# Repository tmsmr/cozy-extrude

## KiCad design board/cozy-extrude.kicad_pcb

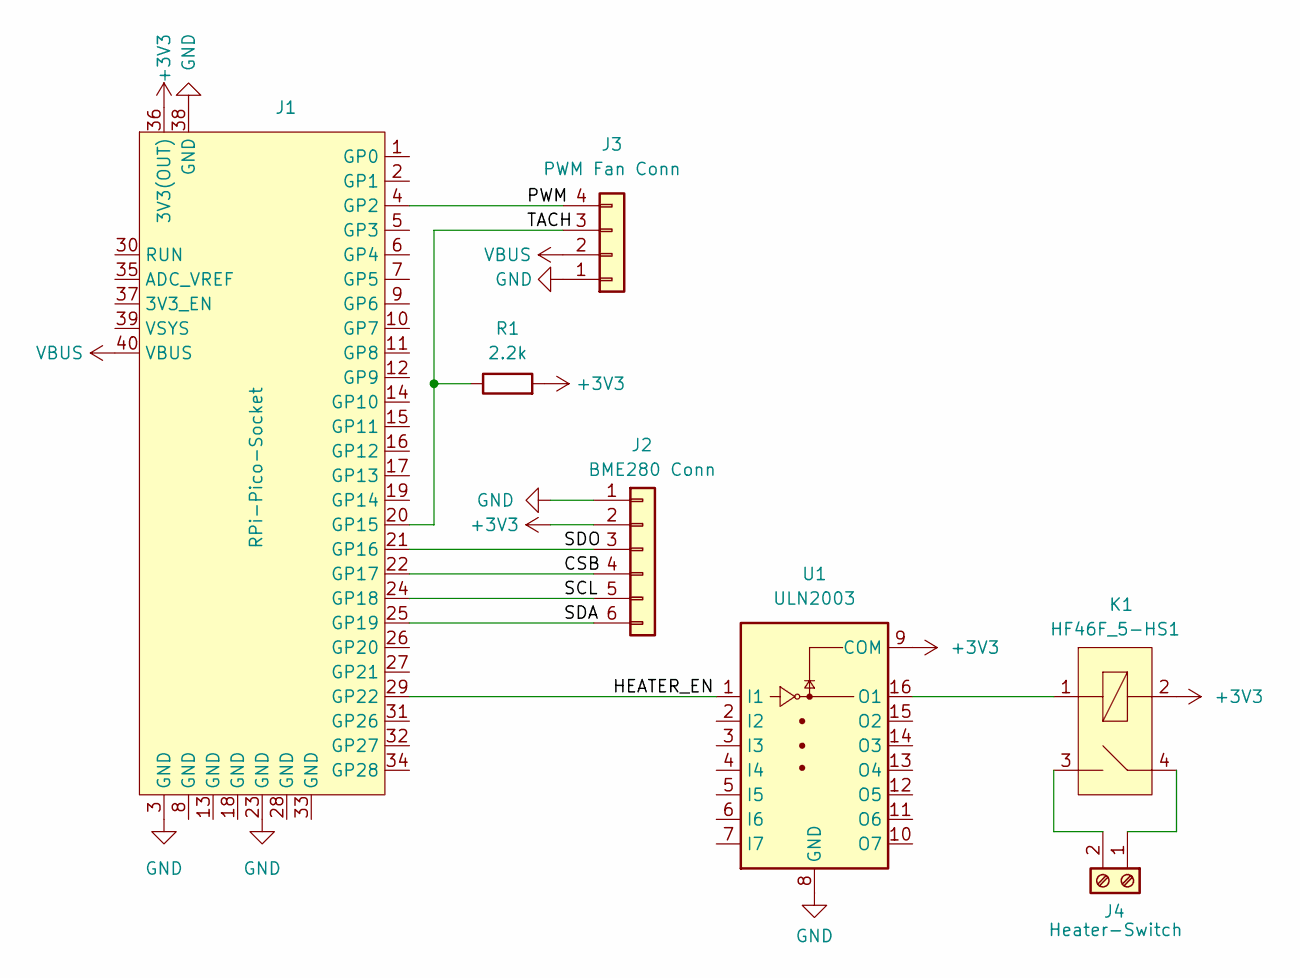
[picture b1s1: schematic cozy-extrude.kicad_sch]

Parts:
J1: RPi-Pico-Socket
J2: BME280 Conn; PinHeader_1x06_P2.54mm_Vertical
J3: PWM Fan Conn; Molex_KK-254_AE-6410-04A_1x04_P2.54mm_Vertical
J4: Heater-Switch; TerminalBlock_Phoenix_MKDS-1,5-2-5.08_1x02_P5.08mm_Horizont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
K1: HF46F_5-HS1; HF46F
R1: 2.2k; R_Axial_DIN0309_L9.0mm_D3.2mm_P15.24mm_Horizontal
U1: ULN2003; DIP-16_W7.62mm

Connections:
+3V3: J1.36 (3V3(OUT)), J2.2, K1.2, R1.2, U1.9 (COM)
/CSB: J1.22 (GP17), J2.4
/HEATER_EN: J1.29 (GP22), U1.1 (I1)
/PWM: J1.4 (GP2), J3.4
/SCL: J1.24 (GP18), J2.5
/SDA: J1.25 (GP19), J2.6
/SDO: J1.21 (GP16), J2.3
/TACH: J1.20 (GP15), J3.3, R1.1
GND: J1.3 (GND), J1.23 (GND), J1.38 (GND), J2.1, J3.1, U1.8 (GND)
unnamed: K1.1, U1.16 (O1)
unnamed: J4.2, K1.3
unnamed: J4.1, K1.4
VBUS: J1.40 (VBUS), J3.2

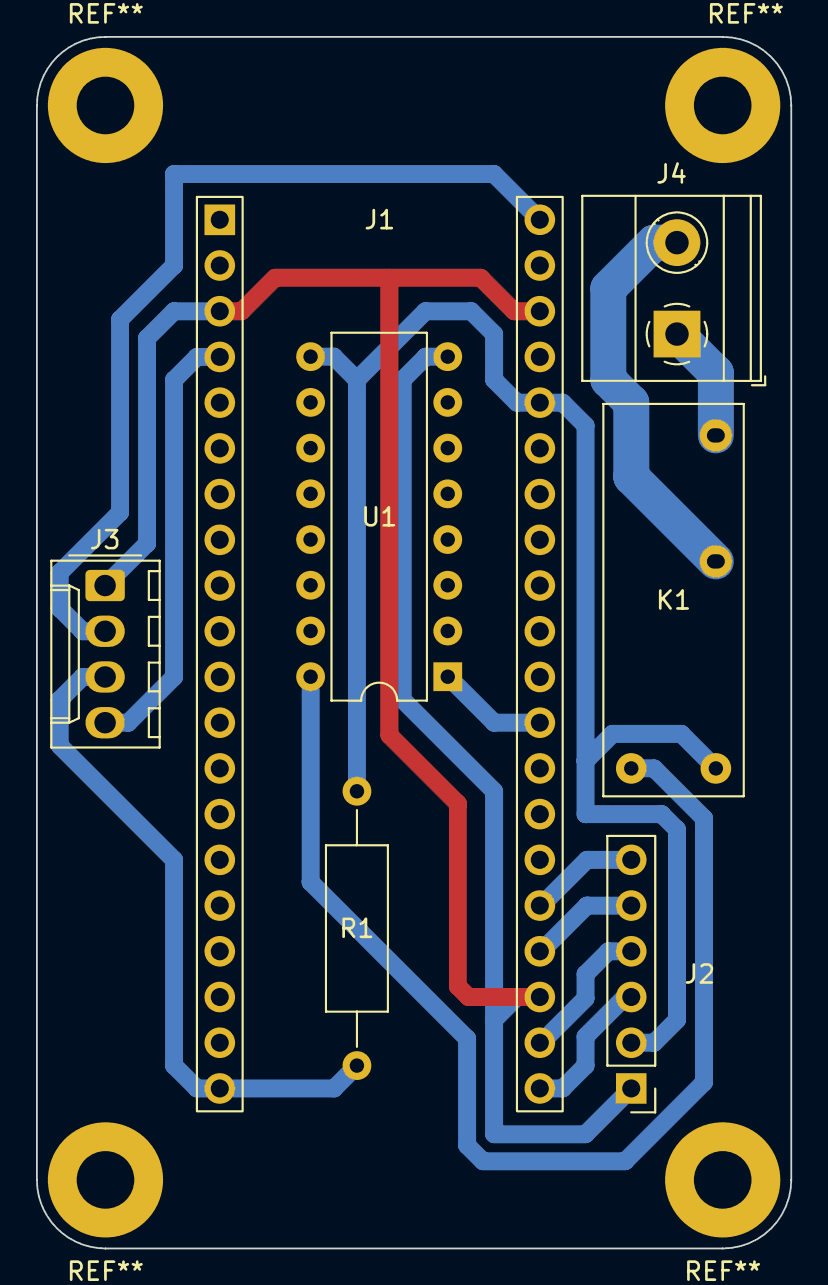
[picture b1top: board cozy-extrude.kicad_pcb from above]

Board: 2 copper layers, 41.9 x 67.3 mm, 7 parts (0 on the bottom side), 13 nets.

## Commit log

2022-12-31 initial commit including fan control
2022-12-31 adds github workflow for tagged builds
2022-12-31 Create LICENSE
2023-01-06 adds bme280 lib
2023-01-06 move fan control to lib/pwm_fan
2023-01-06 adds noctua pwm whitepaper
2023-01-06 PoC for serial commands
2023-01-06 refactor serial commands
2023-01-08 disable LF->CRLF replacement for putchar
2023-01-08 implement protocol in go-based client
2023-01-08 adds fan control loop
2023-01-08 client refactoring
2023-01-08 'status' and 'set' commands for client
2023-01-08 adds command 'server' (http api)
2023-01-21 adds RPi Pico KiCad lib
2023-01-21 move label positions
2023-01-22 adds KiCas lib for HF46F_5-HS1
2023-01-22 initialize KiCad project with custom symbols/footprints
2023-01-22 adds schematic
2023-01-22 some netlabels
2023-01-22 import current footprints
2023-01-22 pcb draft
2023-01-22 make power net 2mm
2023-01-24 improved hf46f footprint and model
2023-01-25 improved pcb
2023-01-27 adds swd port to pico-socket, some image exports for docs
2023-01-28 project reorg
2023-01-28 adjust gitignore files
2023-01-28 set working dir correctly
2023-08-01 Bump golang.org/x/crypto in /control
    Bumps [golang.org/x/crypto](https://github.com/golang/crypto) from 0.0.0-20211215153901-e495a2d5b3d3 to 0.1.0.
    - [Commits](https://github.com/golang/crypto/commits/v0.1.0)
    ---
    updated-dependencies:
    - dependency-name: golang.org/x/crypto
    dependency-type: indirect
2023-08-01 Bump golang.org/x/net from 0.4.0 to 0.7.0 in /control
    Bumps [golang.org/x/net](https://github.com/golang/net) from 0.4.0 to 0.7.0.
    - [Commits](https://github.com/golang/net/compare/v0.4.0...v0.7.0)
    ---
    updated-dependencies:
    - dependency-name: golang.org/x/net
    dependency-type: indirect
2023-08-01 Bump github.com/gin-gonic/gin from 1.8.2 to 1.9.1 in /control
    Bumps [github.com/gin-gonic/gin](https://github.com/gin-gonic/gin) from 1.8.2 to 1.9.1.
    - [Release notes](https://github.com/gin-gonic/gin/releases)
    - [Changelog](https://github.com/gin-gonic/gin/blob/master/CHANGELOG.md)
    - [Commits](https://github.com/gin-gonic/gin/compare/v1.8.2...v1.9.1)
    ---
    updated-dependencies:
2024-02-16 raise default target temp to 35°C
2024-02-20 adds support for heater on gpio 22
2024-02-20 adds support for heating in client/control
2024-02-20 adds missing response for CMD_ENABLE_HEATING
2024-02-20 fix cmd flags for heating
2024-02-20 lower default target temp to 30°C
2024-02-20 Bump golang.org/x/net from 0.10.0 to 0.17.0 in /control
    Bumps [golang.org/x/net](https://github.com/golang/net) from 0.10.0 to 0.17.0.
    - [Commits](https://github.com/golang/net/compare/v0.10.0...v0.17.0)
    ---
    updated-dependencies:
    - dependency-name: golang.org/x/net
    dependency-type: indirect
2024-02-20 Bump golang.org/x/crypto from 0.9.0 to 0.17.0 in /control
    Bumps [golang.org/x/crypto](https://github.com/golang/crypto) from 0.9.0 to 0.17.0.
    - [Commits](https://github.com/golang/crypto/compare/v0.9.0...v0.17.0)
    ---
    updated-dependencies:
    - dependency-name: golang.org/x/crypto
    dependency-type: indirect
2024-02-20 mod tidy
